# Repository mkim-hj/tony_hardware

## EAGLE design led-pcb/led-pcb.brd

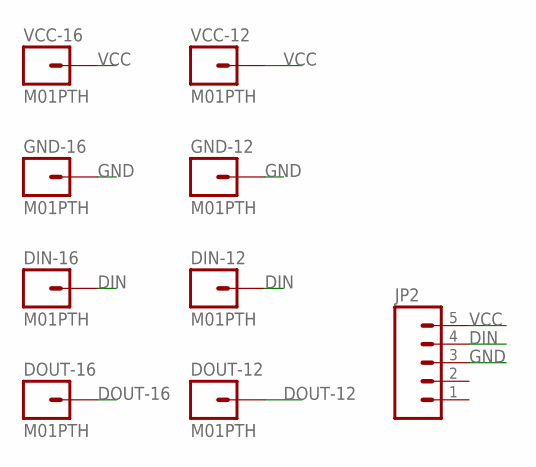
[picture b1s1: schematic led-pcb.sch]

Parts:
DIN-12, DIN-16: M01PTH; 1X01
DOUT-12, DOUT-16: M01PTH; 1X01
GND-12, GND-16: M01PTH; 1X01
JP2: M05PTH; 1X05
VCC-12, VCC-16: M01PTH; 1X01

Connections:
DIN: DIN-12.1, DIN-16.1, JP2.4
DOUT-12: DOUT-12.1
DOUT-16: DOUT-16.1
GND: GND-12.1, GND-16.1, JP2.3
VCC: JP2.5, VCC-12.1, VCC-16.1

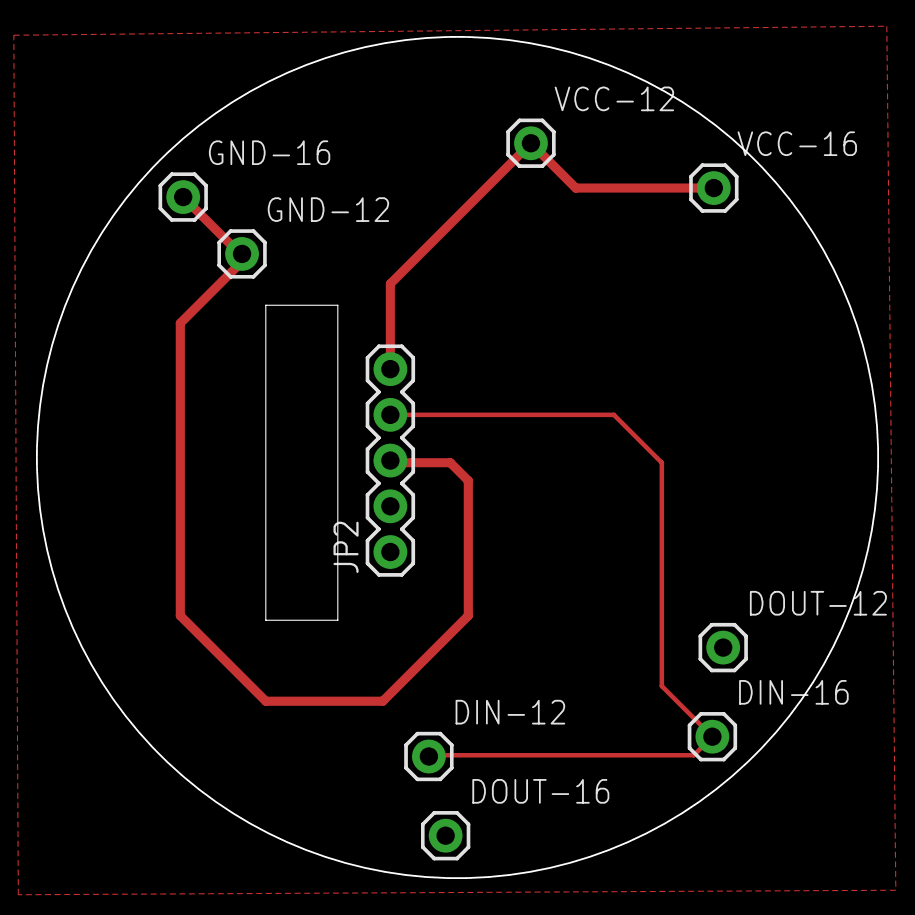
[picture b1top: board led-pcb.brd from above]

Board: 2 copper layers, 46.7 x 46.7 mm, 9 parts (0 on the bottom side), 3 nets.

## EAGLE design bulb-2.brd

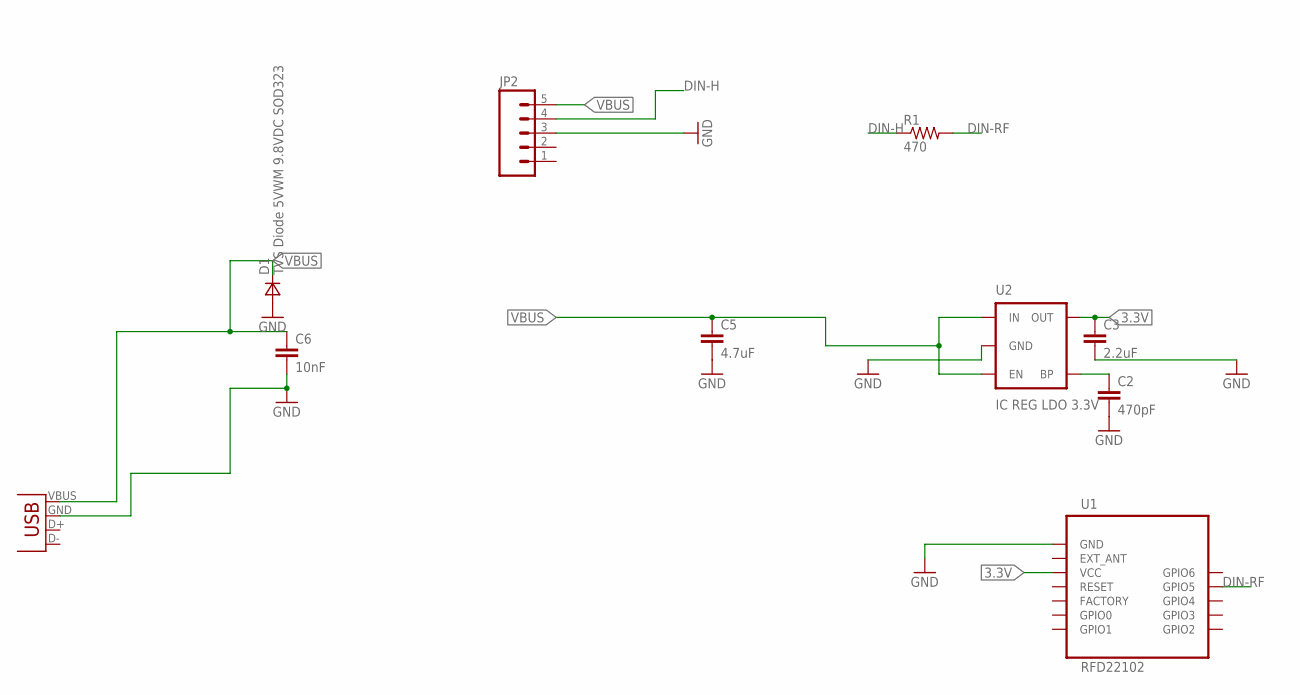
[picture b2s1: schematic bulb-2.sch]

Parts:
C2: 470pF; 0603-CAP
C3: 2.2uF; 0603-CAP
C5: 4.7uF; 0603-CAP
C6: 10nF; 0603-CAP
D1: TVS Diode 5VWM 9.8VDC SOD323; SOD323
JP1: USB-A-H
JP2: M05PTH; 1X05
R1: 470; R0603
U1: RFD22102
U2: IC REG LDO 3.3V; SOT23-5

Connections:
3.3V: C3.1, U1.VCC, U2.5 (OUT)
DIN-H: JP2.4, R1.1
DIN-RF: R1.2, U1.GPIO5
GND: C2.2, C3.2, C5.2, C6.2, D1.2 (A), JP1.GND (VBUS), JP2.3, U1.GND, U2.2 (GND)
unnamed: C2.1, U2.4 (BP)
VBUS: C5.1, C6.1, D1.1 (C), JP1.VBUS (GND), JP2.5, U2.1 (IN), U2.3 (EN)

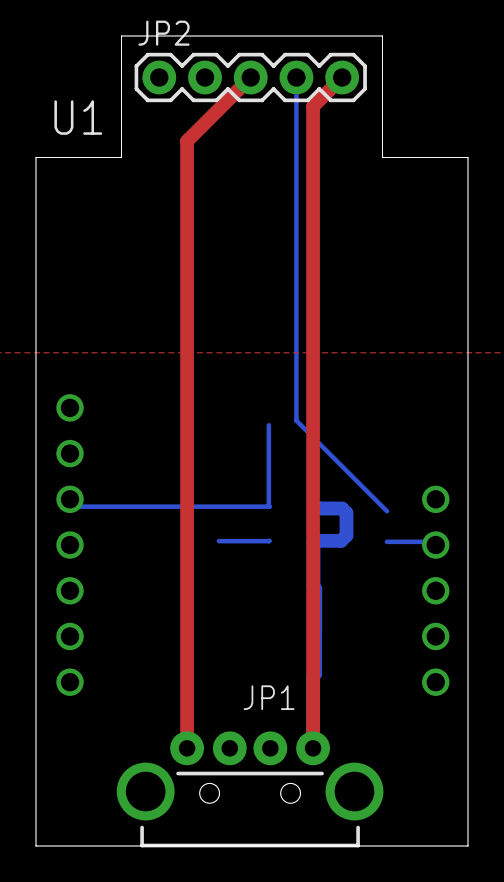
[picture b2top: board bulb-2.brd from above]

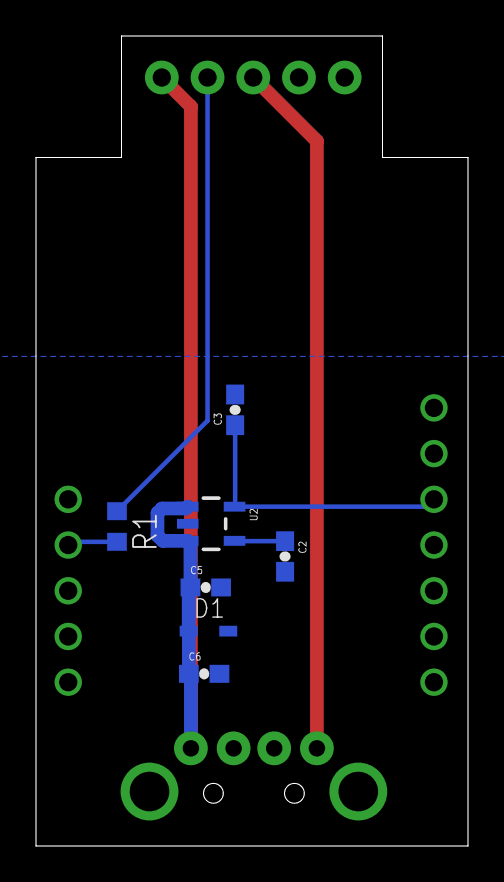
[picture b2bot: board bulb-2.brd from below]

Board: 2 copper layers, 24.0 x 45.0 mm, 10 parts (7 on the bottom side), 6 nets.

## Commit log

2014-11-23 Eagle CAD Files
2014-11-25 circle pcb, and updated usb pcb
2014-11-25 adding dimensions to circle PCB
2014-11-26 updated pcbs
2014-11-26 new eagle .s#7 and s.#9 files
2014-12-03 adding bulb-2.brd and bulb-2.sch

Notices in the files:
parts and their libraries:
SparkFun-PowerIC: Licensing: Creative Commons ShareAlike 4.0 International - https://creativecommons.org/licenses/by-sa/4.0
